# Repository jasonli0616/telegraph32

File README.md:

# telegraph32

Telegraph project for TEJ4M1.

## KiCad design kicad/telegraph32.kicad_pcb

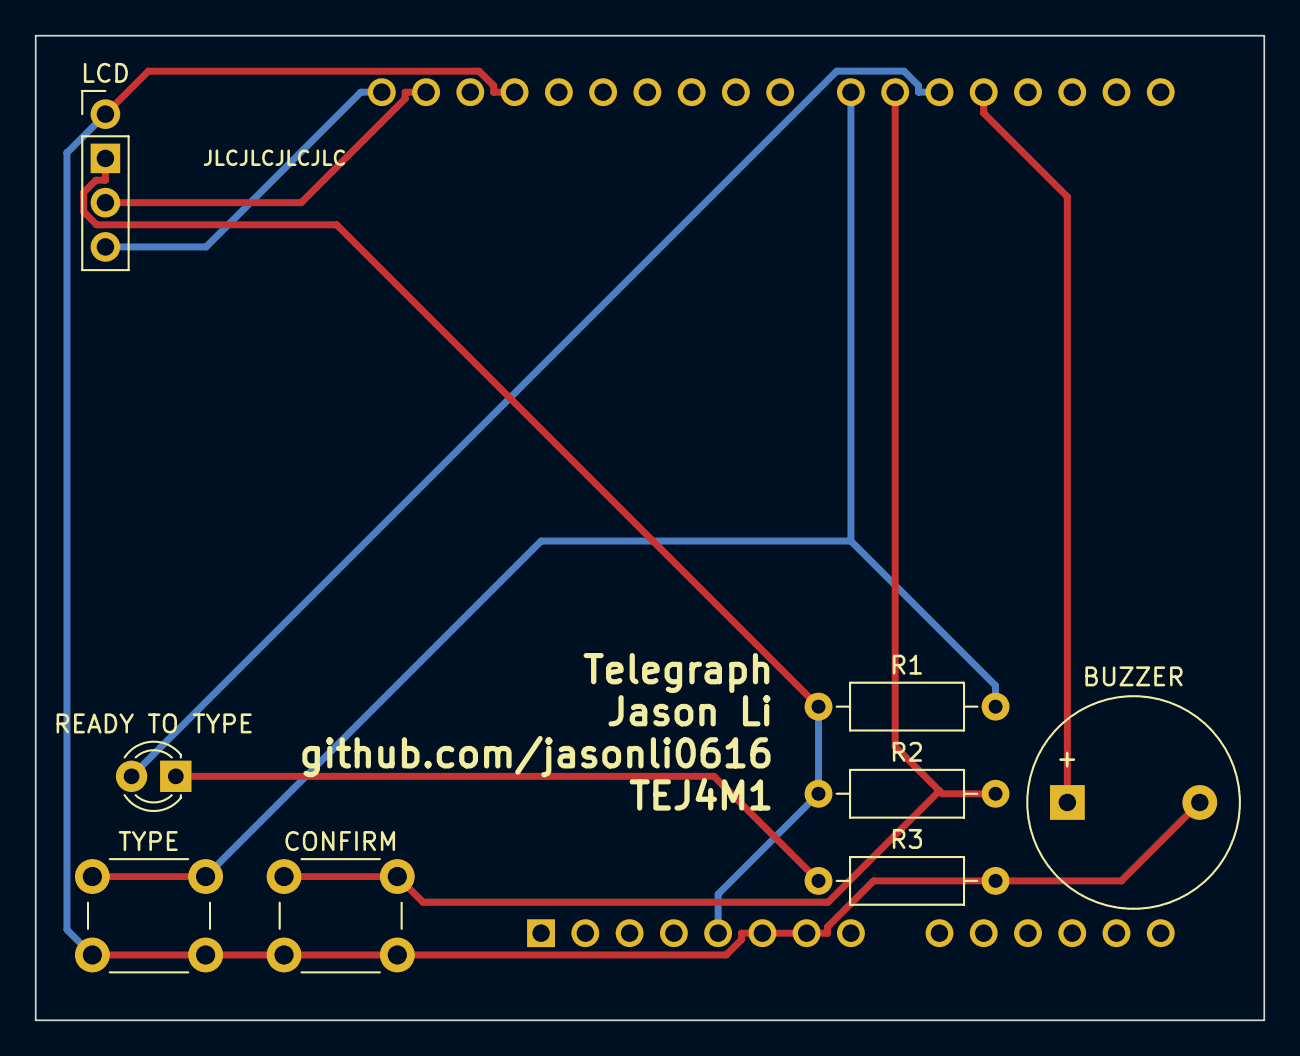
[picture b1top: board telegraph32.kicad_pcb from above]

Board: 2 copper layers, 70.5 x 56.5 mm, 9 parts (1 on the bottom side), 9 nets.

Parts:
BUZZER: Buzzer; Buzzer_12x9.5RM7.6
CONFIRM: SW_Push; SW_PUSH_6mm
ESPDUINO-32: ESPDUINO-32
LCD: PCF8574; PinHeader_1x04_P2.54mm_Vertical
R1, R2: 10K; R_Axial_DIN0207_L6.3mm_D2.5mm_P10.16mm_Horizontal
R3: 470; R_Axial_DIN0207_L6.3mm_D2.5mm_P10.16mm_Horizontal
READY TO TYPE: LED; LED_D3.0mm
TYPE: SW_Push; SW_PUSH_6mm

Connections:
GND: BUZZER.2 (-), CONFIRM.2, ESPDUINO-32.6 (GND), ESPDUINO-32.7 (GND), ESPDUINO-32.29 (GND), LCD.1 (A0), R3.2, TYPE.2
unnamed: ESPDUINO-32.22 (IO14), R1.2, TYPE.1
unnamed: ESPDUINO-32.20 (IO16), READY TO TYPE.2 (A)
unnamed: BUZZER.1 (+), ESPDUINO-32.19 (IO17)
unnamed: CONFIRM.1, ESPDUINO-32.21 (IO27), R2.2
unnamed: ESPDUINO-32.32 (SCL), LCD.4 (P0)
unnamed: ESPDUINO-32.31 (SDA), LCD.3 (A2)
unnamed: R3.1, READY TO TYPE.1 (K)
VCC: ESPDUINO-32.5 (+5V), LCD.2 (A1), R1.1, R2.1

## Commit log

2024-01-18 Upload
2024-01-19 Fix space
2024-01-21 Add images
2024-01-21 Update images
2024-02-01 Fix space timing issue
2024-02-01 Add auto pairing functionality
2024-02-01 Fix lcd issue
